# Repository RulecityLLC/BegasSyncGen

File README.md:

# BegasSyncGen
Sync generator replacement for Bega's Battle hardware.  So that Bega's Battle will work with non-original laserdisc players, including Dexter.

# Introduction
For a full explanation, see http://www.rulecity.com/begas/ .

# PCB
I created the PCB with KiCad v5.  I tested the files on KiCad v8 and they seem to work fine.

# VHDL
I've included the VHDL source code programs I wrote for the CPLD.  I built with Xilinx ISE 14.7 which, last I checked, can be obtained for free as a linux VM that runs fine under Windows in VirtualBox.

# Bill of Materials
These are the actual spreadsheets I used when ordering parts for these PCBs.

# Support
If you need help building the VHDL code, programming the CPLDs, or having PCBs made from the KiCad files, I offer commercial support: https://www.daphne-emu.com:9443/mediawiki/index.php/CommercialSupport

--Matt Ownby

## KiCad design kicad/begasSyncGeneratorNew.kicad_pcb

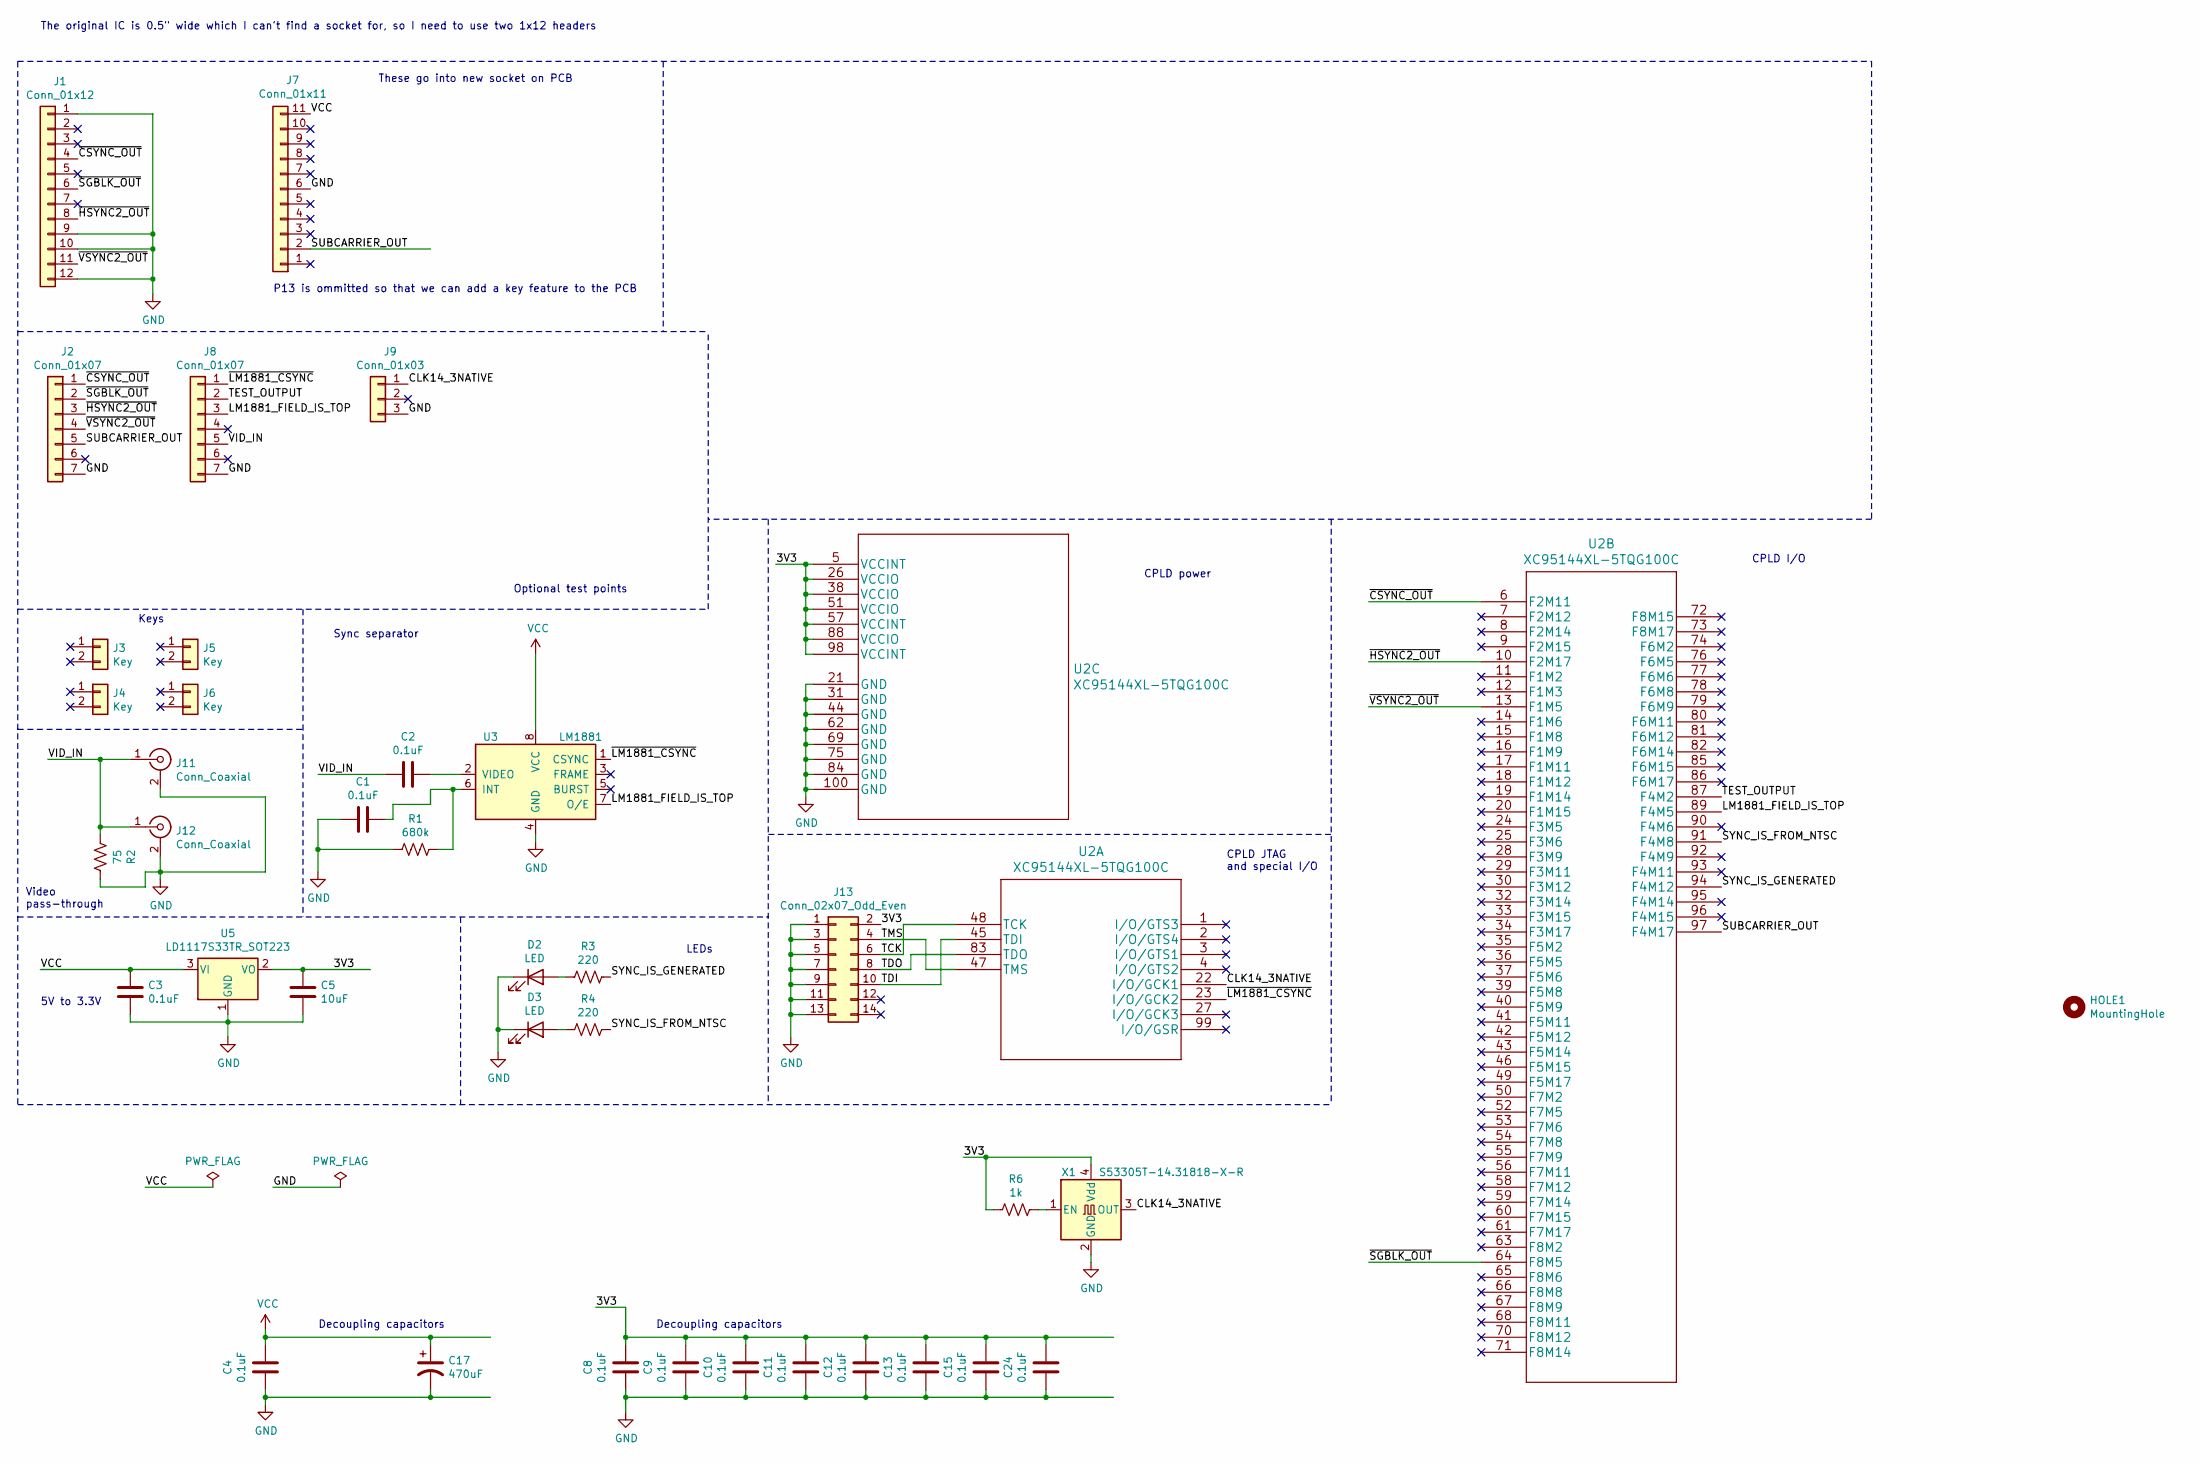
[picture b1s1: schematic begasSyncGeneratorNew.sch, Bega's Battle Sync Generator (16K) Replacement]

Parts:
C1, C2, C3, C4, C8, C9, C10, C11, C12, C13, C15, C24: 0.1uF; C_1206_3216Metric_Pad1.42x1.75mm_HandSolder
C5: 10uF; C_1206_3216Metric_Pad1.42x1.75mm_HandSolder
C17: 470uF; CP_Radial_D8.0mm_P5.00mm
D2, D3: LED; LED_1206_3216Metric_Pad1.42x1.75mm_HandSolder
HOLE1: MountingHole; MountingHole_8.4mm_M8
J1: Conn_01x12; PinHeader_1x12_P2.54mm_Vertical
J2, J8: Conn_01x07; PinHeader_1x07_P2.54mm_Vertical
J3, J4, J5, J6: Key; PinHeader_1x02_P2.54mm_Vertical
J7: Conn_01x11; PinHeader_1x11_P2.54mm_Vertical
J9: Conn_01x03; PinHeader_1x03_P2.54mm_Vertical
J11, J12: Conn_Coaxial; BNC_Amphenol_B6252HB-NPP3G-50_Horizontal
J13: Conn_02x07_Odd_Even; PinHeader_2x07_P2.54mm_Vertical
R1: 680k; R_1206_3216Metric_Pad1.42x1.75mm_HandSolder
R2: 75; R_1206_3216Metric_Pad1.42x1.75mm_HandSolder
R3, R4: 220; R_1206_3216Metric_Pad1.42x1.75mm_HandSolder
R6: 1k; R_1206_3216Metric_Pad1.42x1.75mm_HandSolder
U2: XC95144XL-5TQG100C
U3: LM1881; SO-8_3.9x4.9mm_P1.27mm
U5: LD1117S33TR_SOT223; SOT-223-3_TabPin2
X1: S53305T-14.31818-X-R; Oscillator_SMD_TXC_7C-4Pin_5.0x3.2mm

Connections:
/3V3: C5.1, C8.1, C9.1, C10.1, C11.1, C12.1, C13.1, C15.1, C24.1, J13.2, R6.2, U2.5 (VCCINT), U2.26 (VCCIO), U2.38 (VCCIO), U2.51 (VCCIO), U2.57 (VCCINT), U2.88 (VCCIO), U2.98 (VCCINT), U5.2 (VO), X1.4 (Vdd)
/CLK14_3NATIVE: J9.1, U2.22 (I/O/GCK1), X1.3 (OUT)
/LM1881_FIELD_IS_TOP: J8.3, U2.89 (F4M5), U3.7 (O/E)
/SUBCARRIER_OUT: J2.5, J7.2, U2.97 (F4M17)
/SYNC_IS_FROM_NTSC: R4.1, U2.91 (F4M8)
/SYNC_IS_GENERATED: R3.1, U2.94 (F4M12)
/TCK: J13.6, U2.48 (TCK)
/TDI: J13.10, U2.45 (TDI)
/TDO: J13.8, U2.83 (TDO)
/TEST_OUTPUT: J8.2, U2.87 (F4M2)
/TMS: J13.4, U2.47 (TMS)
/VID_IN: C2.2, J8.5, J11.1 (In), J12.1 (In), R2.2
/~CSYNC_OUT: J1.4, J2.1, U2.6 (F2M11)
/~HSYNC2_OUT: J1.8, J2.3, U2.10 (F2M17)
/~LM1881_CSYNC: J8.1, U2.23 (I/O/GCK2), U3.1 (CSYNC)
/~SGBLK_OUT: J1.6, J2.2, U2.64 (F8M5)
/~VSYNC2_OUT: J1.11, J2.4, U2.13 (F1M5)
GND: C1.2, C3.2, C4.2, C5.2, C8.2, C9.2, C10.2, C11.2, C12.2, C13.2, C15.2, C17.2, C24.2, D2.1 (K), D3.1 (K), J1.1, J1.9, J1.10, J1.12, J2.7, J7.6, J8.7, J9.3, J11.2 (Ext), J12.2 (Ext), J13.1, J13.3, J13.5, J13.7, J13.9, J13.11, J13.13, R1.2, R2.1, U2.21 (GND), U2.31 (GND), U2.44 (GND), U2.62 (GND), U2.69 (GND), U2.75 (GND), U2.84 (GND), U2.100 (GND), U3.4 (GND), U5.1 (GND), X1.2 (GND)
unnamed: C1.1, R1.1, U3.6 (INT)
unnamed: C2.1, U3.2 (VIDEO)
unnamed: D2.2 (A), R3.2
unnamed: D3.2 (A), R4.2
unnamed: R6.1, X1.1 (EN)
VCC: C3.1, C4.1, C17.1, J7.11, U3.8 (VCC), U5.3 (VI)

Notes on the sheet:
P13 is ommitted so that we can add a key feature to the PCB
The original IC is 0.5" wide which I can't find a socket for, so I need to use two 1x12 headers
These go into new socket on PCB
Optional test points
Sync separator
Keys
Video pass-through
CPLD power
CPLD JTAG and special I/O
5V to 3.3V
CPLD I/O
LEDs
Decoupling capacitors

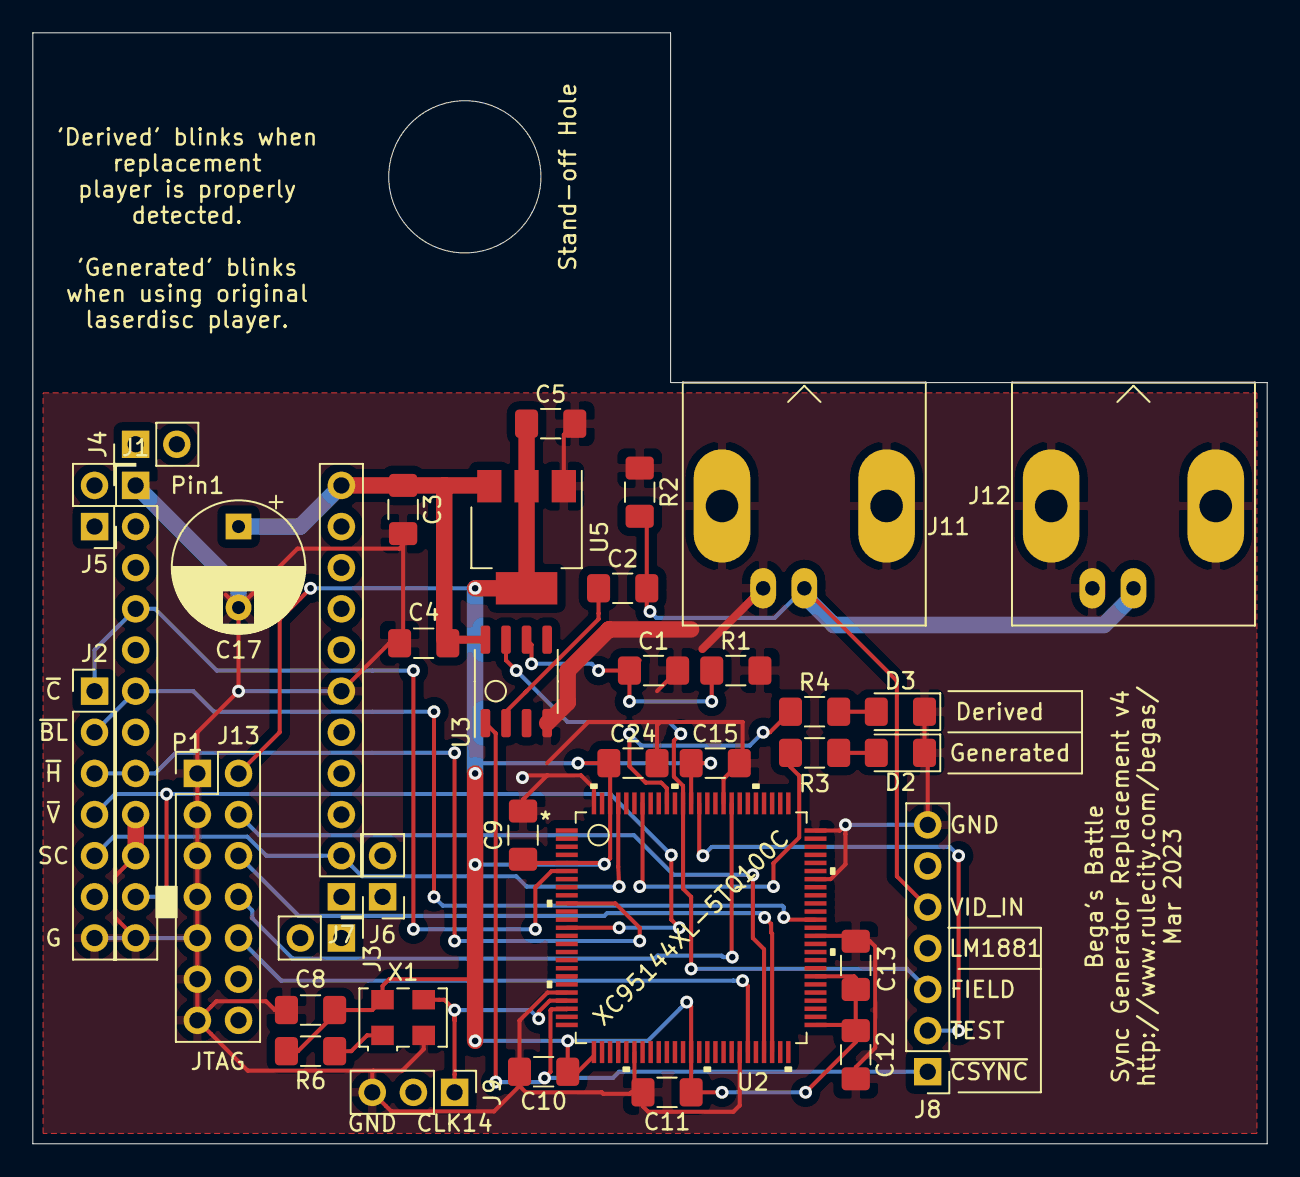
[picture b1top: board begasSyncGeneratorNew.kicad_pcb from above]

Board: 2 copper layers, 76.2 x 68.6 mm, 38 parts (0 on the bottom side), 24 nets.

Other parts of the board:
Stand-off Hole: MountingHole; MountingHole_8.4mm_M8

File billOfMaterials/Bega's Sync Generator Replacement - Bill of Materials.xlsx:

Quantity | Reference | Manufacturer | Manufacturer Part Number | Distributor | Dist. Part Number | Note
Surface mount
11.0 | C1, C2, C4, C8, C9, C10, C11, C12, C13, C15, C24 | Wurth | 8.85012208009E11 | Digi-Key | 732-8086-1-ND | 0.1 uF
2.0 | C3, C5 | Vishay | TL3A106K010C2000 | Digi-Key | 718-TL3A106K010C2000CT-ND | 10 uF
1.0 | D2 | Kingbright Company LLC | APT3216SECK/J3-PRV | Digi-Key | 754-1796-1-ND | "Generated" LED (Red)
1.0 | D3 | Kingbright Company LLC | APT3216SGC | Digi-Key | 754-1141-1-ND | "Derived" LED (Green)
1.0 | R1 |  |  | Digi-Key | P680KETR-ND | 680k Ohm
1.0 | R2 |  |  | Digi-Key | P75ETR-ND | 75 Ohm
2.0 | R3,R4 |  |  | Digi-Key | P220ETR-ND | 220 Ohm
1.0 | R6 |  |  | Digi-Key | P1.0KETR-ND | 1k Ohm
1.0 | U2 |  |  |  |  | XC95144XL-5TQG100C (XC95144XL-10TQG100C is also okay)
1.0 | U3 |  |  | Digi-Key | 296-47437-2-ND | LM1881
1.0 | U5 |  |  | Digi-Key | NCP1117LPST33T3GOSCT-ND | 3.3V voltage regulator
1.0 | X1 |  |  | Digi-Key | 3997-S53305T-14.31818-X-RTR-ND | S53305T-14.31818-X-R
Through hole
1.0 | C17 |  |  | Digi-Key | 493-15702-ND | 470uF
5.0 | J1,J7, J2, J8, J10+J9 |  |  | Digi-Key | 952-3302-ND | 1x12
1.0 | n/a |  |  | Digi-Key | S7045-ND | 1x12 socket
1.0 | n/a |  |  | Digi-Key | S7044-ND | 1x11 socket
4.0 | J3,J4,J5,J6 |  |  | Digi-Key | S7000-ND | 1x02 socket
2.0 | J11,J12 |  |  | Digi-Key | ACX1971-ND | BNC connector
1.0 | J13 |  |  | Digi-Key | 2057-PH2-14-UA-ND | JTAG Interface
Legend
Substitution is allowed
Substitution is allowed but this may change values of C3 and C5, so be careful
Substitution is allowed but clock accuracy is important

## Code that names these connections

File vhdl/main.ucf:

NET csync_prime_out			LOC="P06";
NET hsync2_prime_out			LOC="P10";
NET vsync2_prime_out			LOC="P13";
NET clk14_3native				LOC="P22" | BUFG=CLK;
NET lm1881csync_prime		LOC="P23" | BUFG=CLK;
NET sgblk_prime_out			LOC="P64";
//NET test_output				LOC="P87"	 ;
NET lm1881field_isTop		LOC="P89";
NET led_sync_is_from_ntsc	LOC="P91"	 ;
NET led_sync_is_generated	LOC="P94"	 ;
NET subcarrier_out			LOC="P97"	 ;

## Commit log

2025-05-05 initial VHDL commit
2025-05-05 added bill of materials
2025-05-05 added kicad v5 files to make PCB
2025-05-05 Added missing cache file
2025-05-05 added a pic of the finished product

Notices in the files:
parts and their libraries:
Copyright 2021 Accelerated Designs. All rights reserved.
